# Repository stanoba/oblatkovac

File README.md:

# Electric Wafer Maker Controller (Oblátkovač)

Electric Wafer Maker Controller (Oblátkovač) runs on an Arduino Nano and is built with PlatformIO. It reads a thermistor, accepts input from a rotary encoder, and displays status on an SH1106/SSD1306 monochrome OLED using the U8g2 graphics library.

## Software

The firmware source is in [Software](Software/) folder.

Build with PlatformIO, see `platformio.ini` for board environments.

## Bundled libraries

For reproducible builds this repo includes the following libraries under `Software/lib/`:

- `RotaryEncoder-1.5.3` — rotary encoder handling
- `ThermistorLibrary-1.0.6` — thermistor-to-temperature conversion
- `U8g2` — OLED display graphics
- `button-debounce-0.2.1` — simple button debounce helper

See `Software/lib/README` for details about each bundled library.

## Development tips

- If you change pin assignments, update `Software/src/pins.h` and rebuild for your target.
- Use PlatformIO's verbose build (`pio run -v`) to see full compiler/linker output when troubleshooting.
- To add a board environment, edit `platformio.ini` and add matching pin defines in the sketch as needed.

## Hardware

PCB design files are in the [Hardware](Hardware/) folder.

## Enclosure / 3D models

The electronics are housed in a [Z2AW enclosure](https://www.kradex.com.pl/product/enclosures_with_side_panels/z2a?lang=en). 3D-print models are in [3D-models](3D-models/).

## License

Project code is provided as-is. Third-party libraries retain their original licenses — see each library's `LICENSE` file in `Software/lib/`.

## Safety

**Warning:** this project involves mains and high-voltage circuitry. Working on or near high voltage can cause serious injury or death.

- **Disconnect power:** Always remove mains power and verify the circuit is de-energized before touching components.
- **Use PPE:** Wear appropriate personal protective equipment (insulating gloves, eye protection) when testing live systems.
- **Isolation:** Keep a safe distance from exposed conductors; use insulated tools and work on insulated surfaces.
- **Discharge capacitors:** Safely discharge capacitors before servicing; they can hold lethal charge after power removal.
- **One hand rule:** When possible, use the one-hand rule to avoid current passing through the chest.
- **Qualified personnel:** If you are not experienced with mains/high-voltage electronics, seek assistance from a qualified technician or electrician.
- **Work sober and focused:** Never work on high-voltage circuits when tired, impaired, or alone.

Follow local regulations and best practices for electrical safety. The authors are not responsible for damage or injury from misuse.

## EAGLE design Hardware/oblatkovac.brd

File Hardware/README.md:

# Oblátkovač PCB (Work in progress)

The PCB for Oblátkovač (Electric Wafer Maker Controller) and schematic were designed using Autodesk EAGLE. Source EAGLE project files (schematic and board) are included in this folder.

- **Gerbers:** Manufacturing Gerber files are available in the [Hardware/gerber files/](Hardware/gerber%20files/) directory for PCB fabrication.
- **Libraries:** The EAGLE libraries used in the design are included in the [Hardware/libraries/](Hardware/libraries/) folder.
- **Notes:** Open the .sch and .brd files in Autodesk EAGLE. To regenerate Gerbers, use EAGLE's CAM processor and export an RS-274X Gerber set.
</br></br>

Eagle libraries Downloaded from:

- ArduinoNanoV30.lbr
    - https://github.com/psrobotics/eagle_lib
- Rembrandt Electronics - JST XH Connectors v1-0.lbr
    - https://github.com/yann-ygn/eagle-libraries/blob/master/Rembrandt%20Electronics%20-%20JST%20XH%20Connectors%20v1-0.lbr
    - https://www.diymodules.org/eagle-show-object?type=usr&id=1012211612&part=Rembrandt+Electronics+-+JST+XH+Connectors+v1-0.lbr&device=JST-XH-02-PIN
- 13oled.lbr
	- https://github.com/suhail-jr/1.3-OLED-Display-Module-Eagle-Library/
- mastrogippo.lbr
    - https://github.com/mastrogippo/MastroGippo-Eagle-library

## Schematic

## PCB

Front side:</br>

Back side:</br>

## Safety

**Warning:** this project involves mains and high-voltage circuitry. Working on or near high voltage can cause serious injury or death.

- **Disconnect power:** Always remove mains power and verify the circuit is de-energized before touching components.
- **Use PPE:** Wear appropriate personal protective equipment (insulating gloves, eye protection) when testing live systems.
- **Isolation:** Keep a safe distance from exposed conductors; use insulated tools and work on insulated surfaces.
- **Discharge capacitors:** Safely discharge capacitors before servicing; they can hold lethal charge after power removal.
- **One hand rule:** When possible, use the one-hand rule to avoid current passing through the chest.
- **Qualified personnel:** If you are not experienced with mains/high-voltage electronics, seek assistance from a qualified technician or electrician.
- **Work sober and focused:** Never work on high-voltage circuits when tired, impaired, or alone.

Follow local regulations and best practices for electrical safety. The authors are not responsible for damage or injury from misuse.

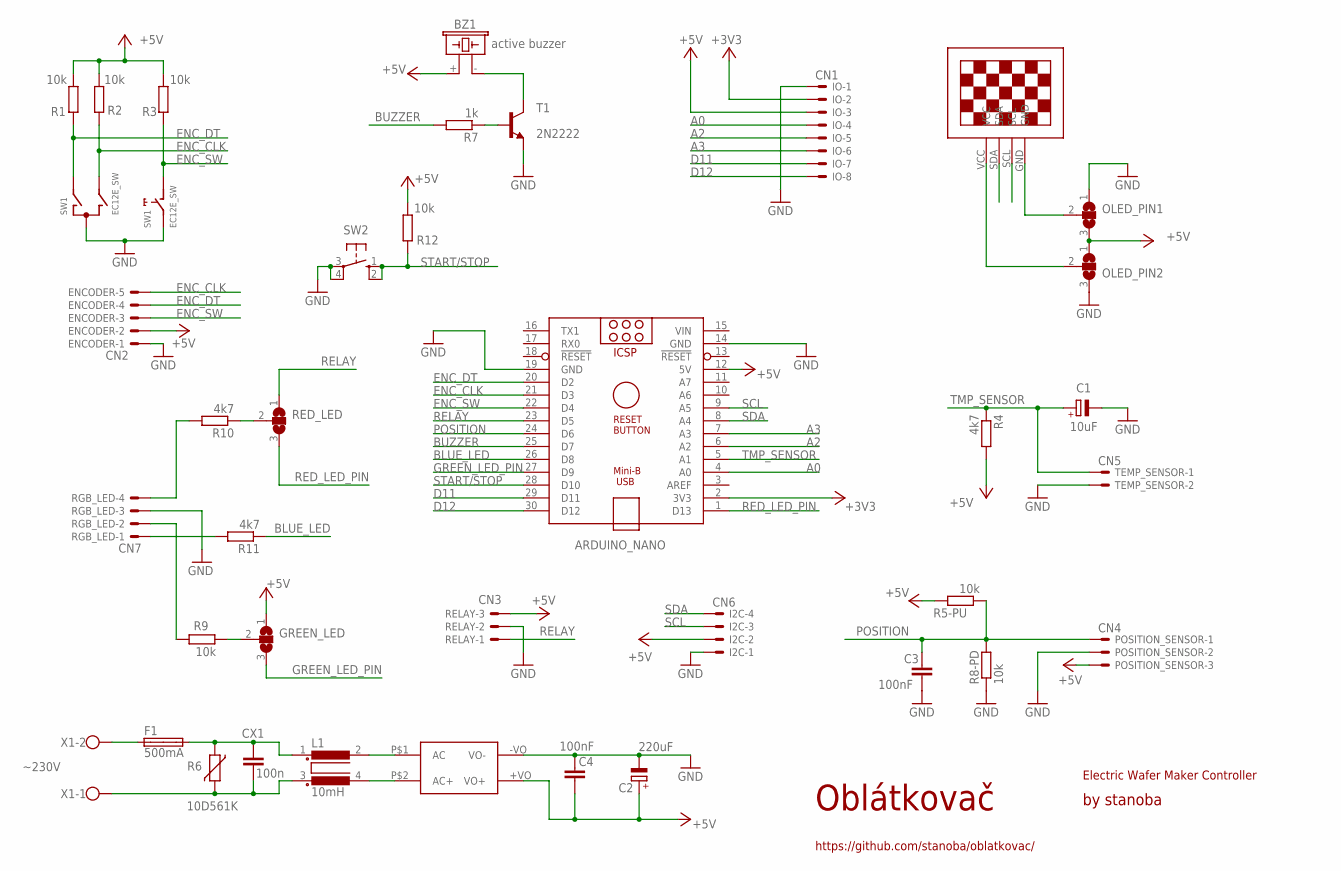
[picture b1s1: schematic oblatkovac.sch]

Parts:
ARDUINO_NANO: ARDUINO_NANO
BZ1: active buzzer; F/CM12P
C1: 10uF; E5-6
C2: 220uF; E5-10,5
C3, C4: 100nF; C050-024X044
CX1: 100n; XC10B6
ENCODER: CN2; JST-XH-05-PACKAGE-LONG-PAD
F1: 500mA; SHK20L
GREEN_LED: SJ2W; SJ_2
I2C: CN6; JST-XH-04-PACKAGE-LONG-PAD
IO: CN1; JST-XH-08-PACKAGE-LONG-PAD
L1: 10mH; B2
OLED_PIN1, OLED_PIN2: SJ2W; SJ_2
POSITION_SENSOR: CN4; JST-XH-03-PACKAGE-LONG-PAD
R1, R2, R3, R5-PU, R8-PD, R9, R12: 10k; 0207/10
R4, R10, R11: 4k7; 0207/10
R6: 10D561K; R-7,5
R7: 1k; 0207/10
RED_LED: SJ2W; SJ_2
RELAY: CN3; JST-XH-03-PACKAGE-LONG-PAD
RGB_LED: CN7; JST-XH-04-PACKAGE-LONG-PAD
SW1: EC12E_SW; ALPS_EC12E_SW
SW2: 10-XX; B3F-10XX
T1: 2N2222; TO92-EBC
TEMP_SENSOR: CN5; JST-XH-02-PACKAGE-LONG-PAD
U$1: 13"OLED13"OLED; 1.3"OLED
U$2: HLK-5M05
X1: ~230V; W237-102

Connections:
+3V3: ARDUINO_NANO.2 (3V3), IO.2
+5V: ARDUINO_NANO.12 (5V), BZ1.+ (1), C2.+, C4.2, ENCODER.2, GREEN_LED.1, I2C.2, IO.3, OLED_PIN1.3, OLED_PIN2.1, POSITION_SENSOR.3, R1.2, R2.2, R3.2, R4.2, R5-PU.2, R12.2, RELAY.3, U$2.+VO (VO+)
A0: ARDUINO_NANO.4 (A0), IO.4
A2: ARDUINO_NANO.6 (A2), IO.5
A3: ARDUINO_NANO.7 (A3), IO.6
BLUE_LED: ARDUINO_NANO.26 (D8), R11.1
BUZZER: ARDUINO_NANO.25 (D7), R7.2
D11: ARDUINO_NANO.29 (D11), IO.7
D12: ARDUINO_NANO.30 (D12), IO.8
ENC_CLK: ARDUINO_NANO.21 (D3), ENCODER.5, R2.1, SW1.B
ENC_DT: ARDUINO_NANO.20 (D2), ENCODER.4, R1.1, SW1.A
ENC_SW: ARDUINO_NANO.22 (D4), ENCODER.3, R3.1, SW1.D (1)
GND: ARDUINO_NANO.14 (GND), ARDUINO_NANO.19 (GND), C1.-, C2.-, C3.2, C4.1, ENCODER.1, I2C.1, IO.1, OLED_PIN1.1, OLED_PIN2.3, POSITION_SENSOR.2, R8-PD.1, RELAY.2, RGB_LED.3, SW1.C, SW1.E (2), SW2.3, SW2.4 (P1), T1.E, TEMP_SENSOR.2, U$2.-VO (VO-)
GREEN_LED_PIN: ARDUINO_NANO.27 (D9), GREEN_LED.3
LIVE_FUSED: F1.1A, X1.2
LIVE_FUSED2: CX1.1, F1.2A, L1.1, R6.1
LIVE_FUSED3: L1.2, U$2.P$1 (AC)
unnamed: R11.2, RGB_LED.1
unnamed: GREEN_LED.2, R9.2
unnamed: R9.1, RGB_LED.2
unnamed: R10.2, RGB_LED.4
unnamed: BZ1.- (2), T1.C
unnamed: R7.1, T1.B
unnamed: R10.1, RED_LED.2
NEUTRAL: CX1.2, L1.3, R6.2, X1.1
NEUTRAL2: L1.4, U$2.P$2 (AC+)
OLED_PIN1: OLED_PIN1.2, U$1.GND
OLED_PIN2: OLED_PIN2.2, U$1.VCC
POSITION: ARDUINO_NANO.24 (D6), C3.1, POSITION_SENSOR.1, R5-PU.1, R8-PD.2
RED_LED_PIN: ARDUINO_NANO.1 (D13), RED_LED.3
RELAY: ARDUINO_NANO.23 (D5), RED_LED.1, RELAY.1
SCL: ARDUINO_NANO.9 (A5), I2C.3, U$1.SCL
SDA: ARDUINO_NANO.8 (A4), I2C.4, U$1.SDA
START/STOP: ARDUINO_NANO.28 (D10), R12.1, SW2.1 (S), SW2.2 (S1)
TMP_SENSOR: ARDUINO_NANO.5 (A1), C1.+, R4.1, TEMP_SENSOR.1
VIN: ARDUINO_NANO.15 (VIN)

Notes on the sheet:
https://github.com/stanoba/oblatkovac/
by stanoba
Oblátkovač
Electric Wafer Maker Controller

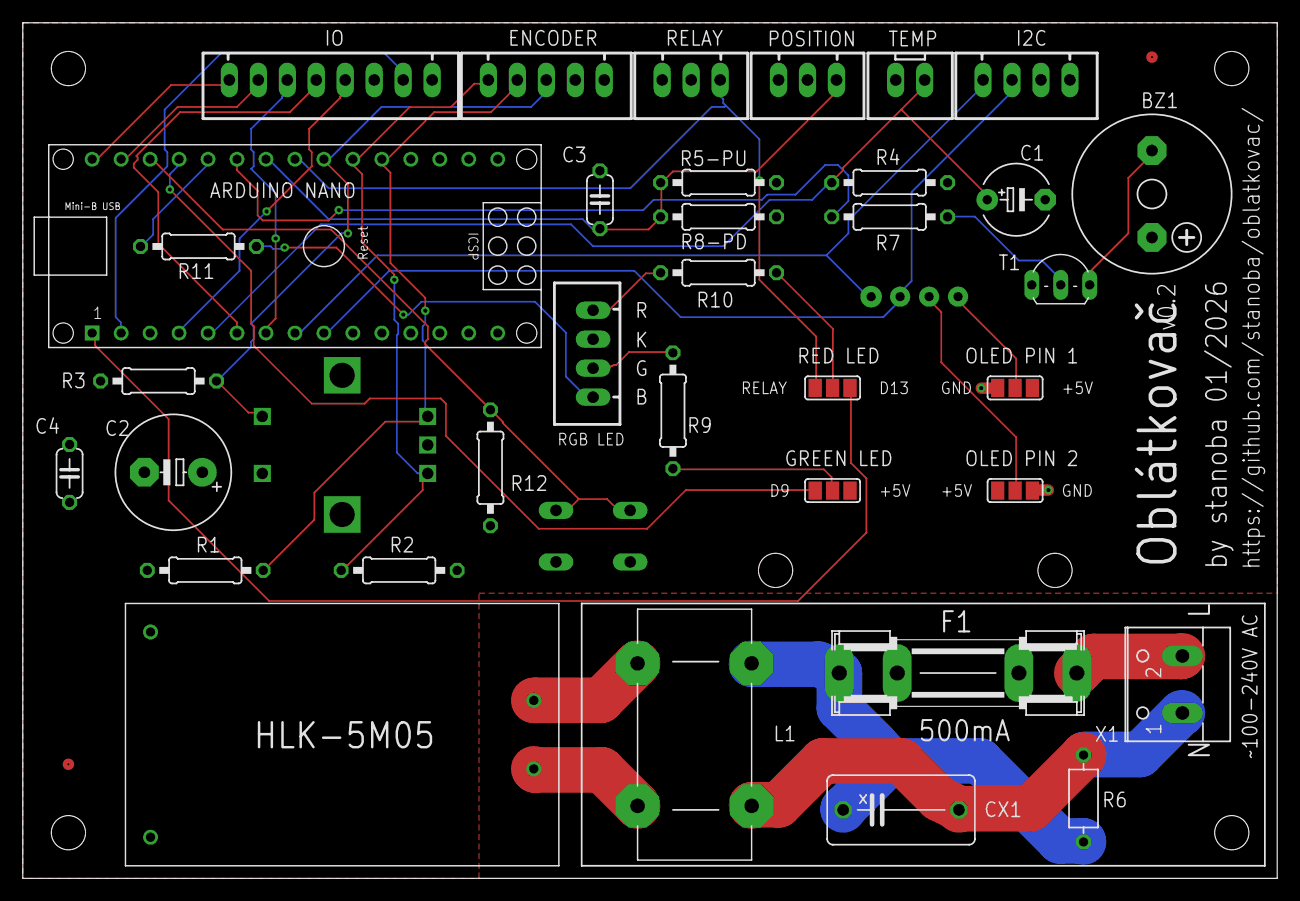
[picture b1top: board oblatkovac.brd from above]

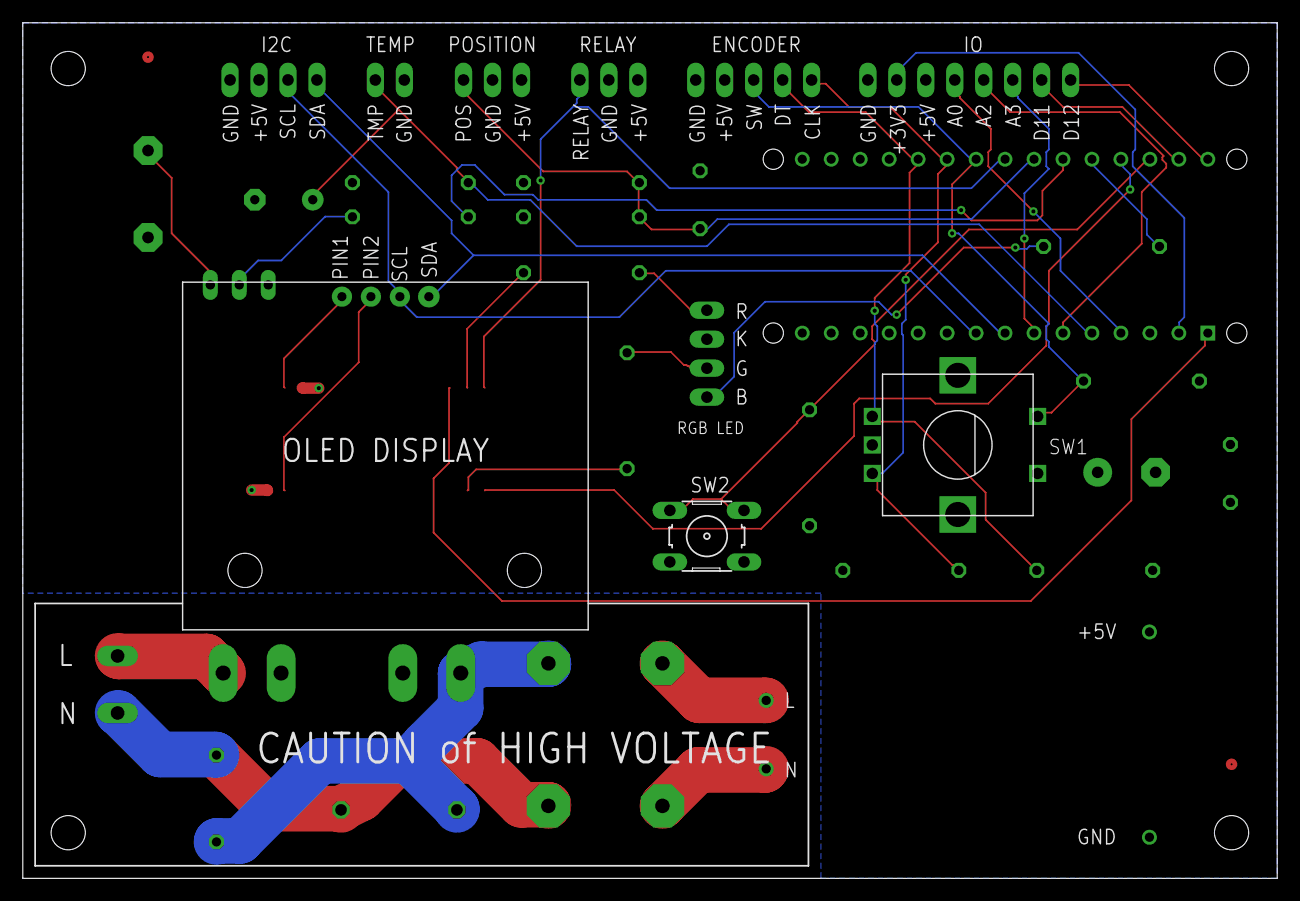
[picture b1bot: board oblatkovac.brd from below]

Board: 2 copper layers, 110.0 x 75.0 mm, 40 parts (3 on the bottom side), 35 nets.

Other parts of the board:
U$3, U$4: FIDUCIAL

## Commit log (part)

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2025-12-07 Update gitignore
2025-12-07 - Improve platform pin definitions - Add time counter - Add OLED image to README
2025-12-08 Optimizations and improvements
2025-12-08 RAM optimization and DEBUG improvements
2025-12-08 Refactor encoder variable names for clarity and update comments
2025-12-21 Add Hardware folder
2026-01-15 Update code according new PCB design
2026-01-15 Fix logical operators for clarity and consistency in heater control logic
2026-01-16 Implement EEPROM storage for target temperature and countdown time
2026-01-17 - Improved temperature sensing, heater control, and UI. - Integrated EEPROM for saving settings. - Configured button handlers for menu navigation and start/stop functionality. - Established pin defin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
2026-01-17 Update README.md and add new schematic PDF to Hardware documentation
2026-01-17 Refactor README.md to improve formatting of PCB images section
